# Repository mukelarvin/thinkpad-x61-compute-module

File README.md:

# thinkpad-x61-compute-module
A motherboard replacement for the Thinkpad X61 laptop, using the Raspberry Pi Computer Module

## Display Considerations

Outer Area
Width 268 mm
Height 210 mm

Bottom Bezel 16 mm
Notification LED area 10 mm
Side Bezel 11 mm

Display Viewable Area
Width 246 mm
Height 185 mm

With modifications the bezel could support about...
Width 256 mm
Height 190 mm

### Candidates
SXGA+ Mod
https://www.panelook.com/HV121P01-101_HYDIS_12.1_LCM_overview_3604.html
https://www.panelook.com/HV121P01-100_HYDIS_12.1_LCM_overview_3603.html
Hearted on aliexpress

Wisecoco 11 Inch AMOLED
Width 231.64 mm
Height 168.60 mm
Too small

Surface Pro LCD 12 inch
Width 254 mm
Height 169 mm
Good Candidate, maybe room for Camera?

Ipad Pro 11"
Width 229.06 mm
Height 159.99 mm
A little small

Ipad Pro 12.9"
Width 262 mm
Height 196 mm
This would be a great candidate but the interface is probably quite difficult
https://www.panelook.com/LTL129JL01-A03_Samsung_12.9_Assembly_overview_31582.html

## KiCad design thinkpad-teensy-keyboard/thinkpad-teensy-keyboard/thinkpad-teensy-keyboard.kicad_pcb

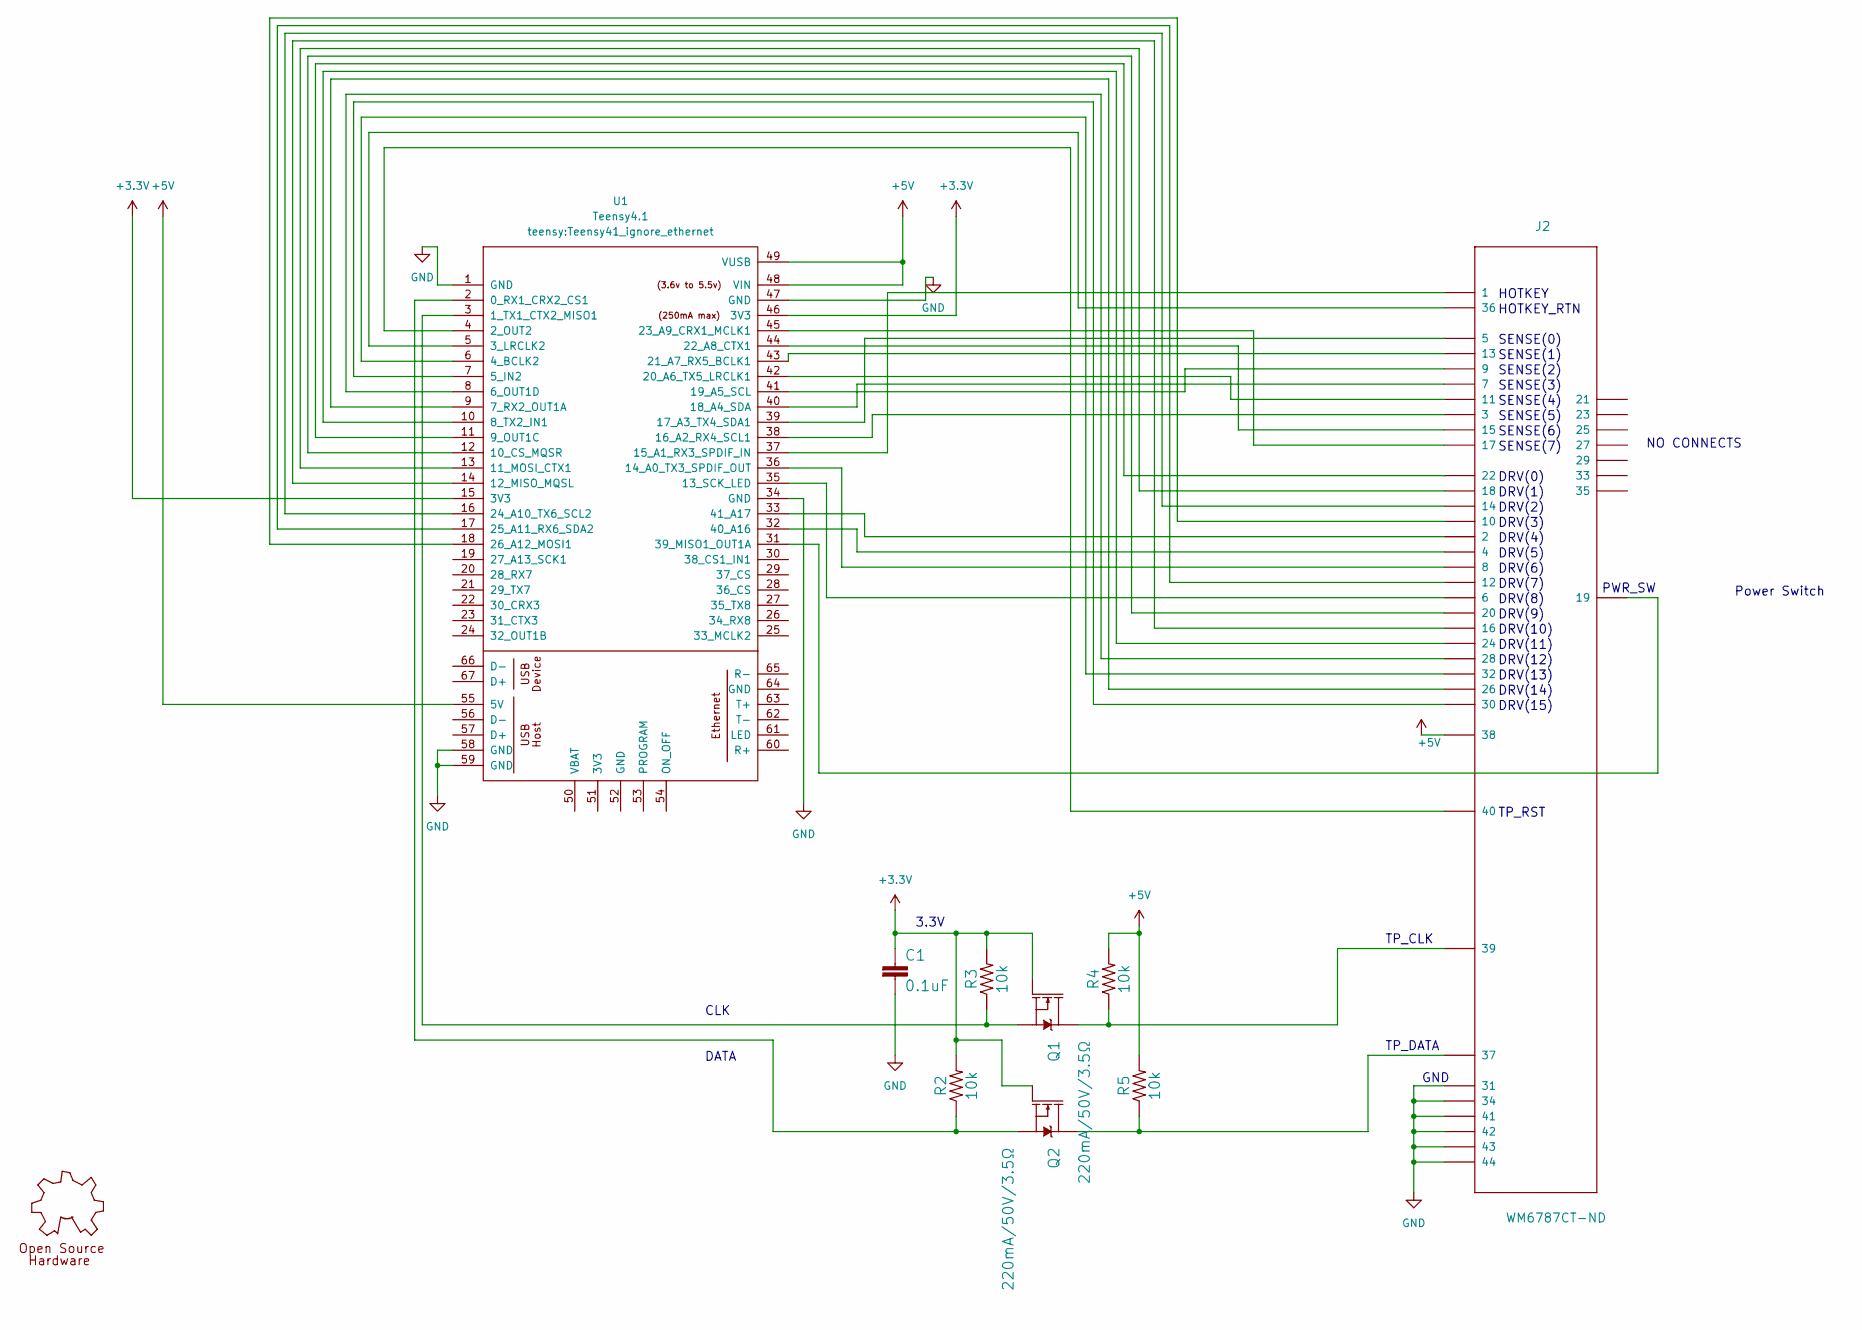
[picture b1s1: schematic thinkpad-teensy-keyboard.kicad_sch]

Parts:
C1: 0.1uF; 0603
GOLD_ORB_SM1: OSHWLOGOLOGO5MM; OSHW_5MM
J2: WM6787CT-ND
Q1, Q2: 220mA/50V/3.5Ω; SOT23-3
R2, R3, R4, R5: 10k; 0603
U1: Teensy4.1; Teensy41_ignore_ethernet

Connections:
+3V3: C1.1, Q1.1 (G), Q2.1 (G), R2.2, R3.2, U1.15 (3V3), U1.46 (3V3)
+5V: J2.P$38 (38), R4.2, R5.2, U1.48 (VIN), U1.49 (VUSB), U1.55 (5V)
GND: C1.2, J2.P$31 (31), J2.P$34 (34), J2.P$41 (43), J2.P$42 (44), J2.P$43 (41), J2.P$44 (42), U1.1 (GND), U1.34 (GND), U1.47 (GND), U1.58 (GND), U1.59 (GND)
unnamed: J2.P$1 (1), U1.37 (15_A1_RX3_SPDIF_IN)
unnamed: J2.P$2 (2), U1.33 (41_A17)
unnamed: J2.P$6 (6), U1.35 (13_SCK_LED)
unnamed: J2.P$8 (8), U1.36 (14_A0_TX3_SPDIF_OUT)
unnamed: J2.P$10 (10), U1.18 (26_A12_MOSI1)
unnamed: J2.P$12 (12), U1.17 (25_A11_RX6_SDA2)
unnamed: J2.P$14 (14), U1.16 (24_A10_TX6_SCL2)
unnamed: J2.P$16 (16), U1.14 (12_MISO_MQSL)
unnamed: J2.P$18 (18), U1.13 (11_MOSI_CTX1)
unnamed: J2.P$19 (19), U1.31 (39_MISO1_OUT1A)
unnamed: J2.P$37 (37), Q2.3 (D), R5.1
unnamed: J2.P$39 (39), Q1.3 (D), R4.1
unnamed: Q1.2 (S), R3.1, U1.3 (1_TX1_CTX2_MISO1)
unnamed: Q2.2 (S), R2.1, U1.2 (0_RX1_CRX2_CS1)
unnamed: J2.P$40 (40), U1.4 (2_OUT2)
unnamed: J2.P$36 (36), U1.5 (3_LRCLK2)
unnamed: J2.P$32 (32), U1.6 (4_BCLK2)
unnamed: J2.P$30 (30), U1.7 (5_IN2)
unnamed: J2.P$28 (28), U1.8 (6_OUT1D)
unnamed: J2.P$26 (26), U1.9 (7_RX2_OUT1A)
unnamed: J2.P$24 (24), U1.10 (8_TX2_IN1)
unnamed: J2.P$22 (22), U1.11 (9_OUT1C)
unnamed: J2.P$20 (20), U1.12 (10_CS_MQSR)
unnamed: J2.P$4 (4), U1.32 (40_A16)
unnamed: J2.P$3 (3), U1.38 (16_A2_RX4_SCL1)
unnamed: J2.P$5 (5), U1.39 (17_A3_TX4_SDA1)
unnamed: J2.P$7 (7), U1.40 (18_A4_SDA)
unnamed: J2.P$9 (9), U1.41 (19_A5_SCL)
unnamed: J2.P$11 (11), U1.42 (20_A6_TX5_LRCLK1)
unnamed: J2.P$13 (13), U1.43 (21_A7_RX5_BCLK1)
unnamed: J2.P$15 (15), U1.44 (22_A8_CTX1)
unnamed: J2.P$17 (17), U1.45 (23_A9_CRX1_MCLK1)

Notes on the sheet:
HOTKEY
DRV(0)
CLK
DRV(4)
DRV(13)
DRV(3)
SENSE(7)
TP_RST
SENSE(0)
TP_DATA
DRV(8)
DRV(6)
DRV(10)
TP_CLK
SENSE(2)
GND
3.3V
SENSE(6)
SENSE(5)
DRV(5)
SENSE(4)
DRV(7)
DRV(2)
DRV(14)
SENSE(3)
PWR_SW
HOTKEY_RTN
SENSE(1)
DRV(9)
DRV(12)
DRV(11)
Power Switch
DRV(1)
DRV(15)
NO CONNECTS
DATA

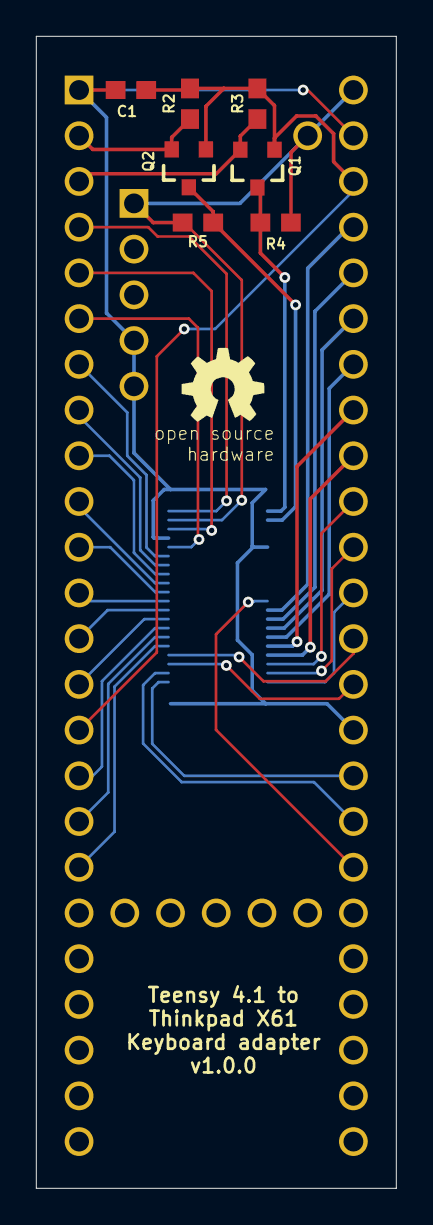
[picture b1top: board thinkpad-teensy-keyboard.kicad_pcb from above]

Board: 2 copper layers, 20.0 x 64.0 mm, 10 parts (1 on the bottom side), 35 nets.

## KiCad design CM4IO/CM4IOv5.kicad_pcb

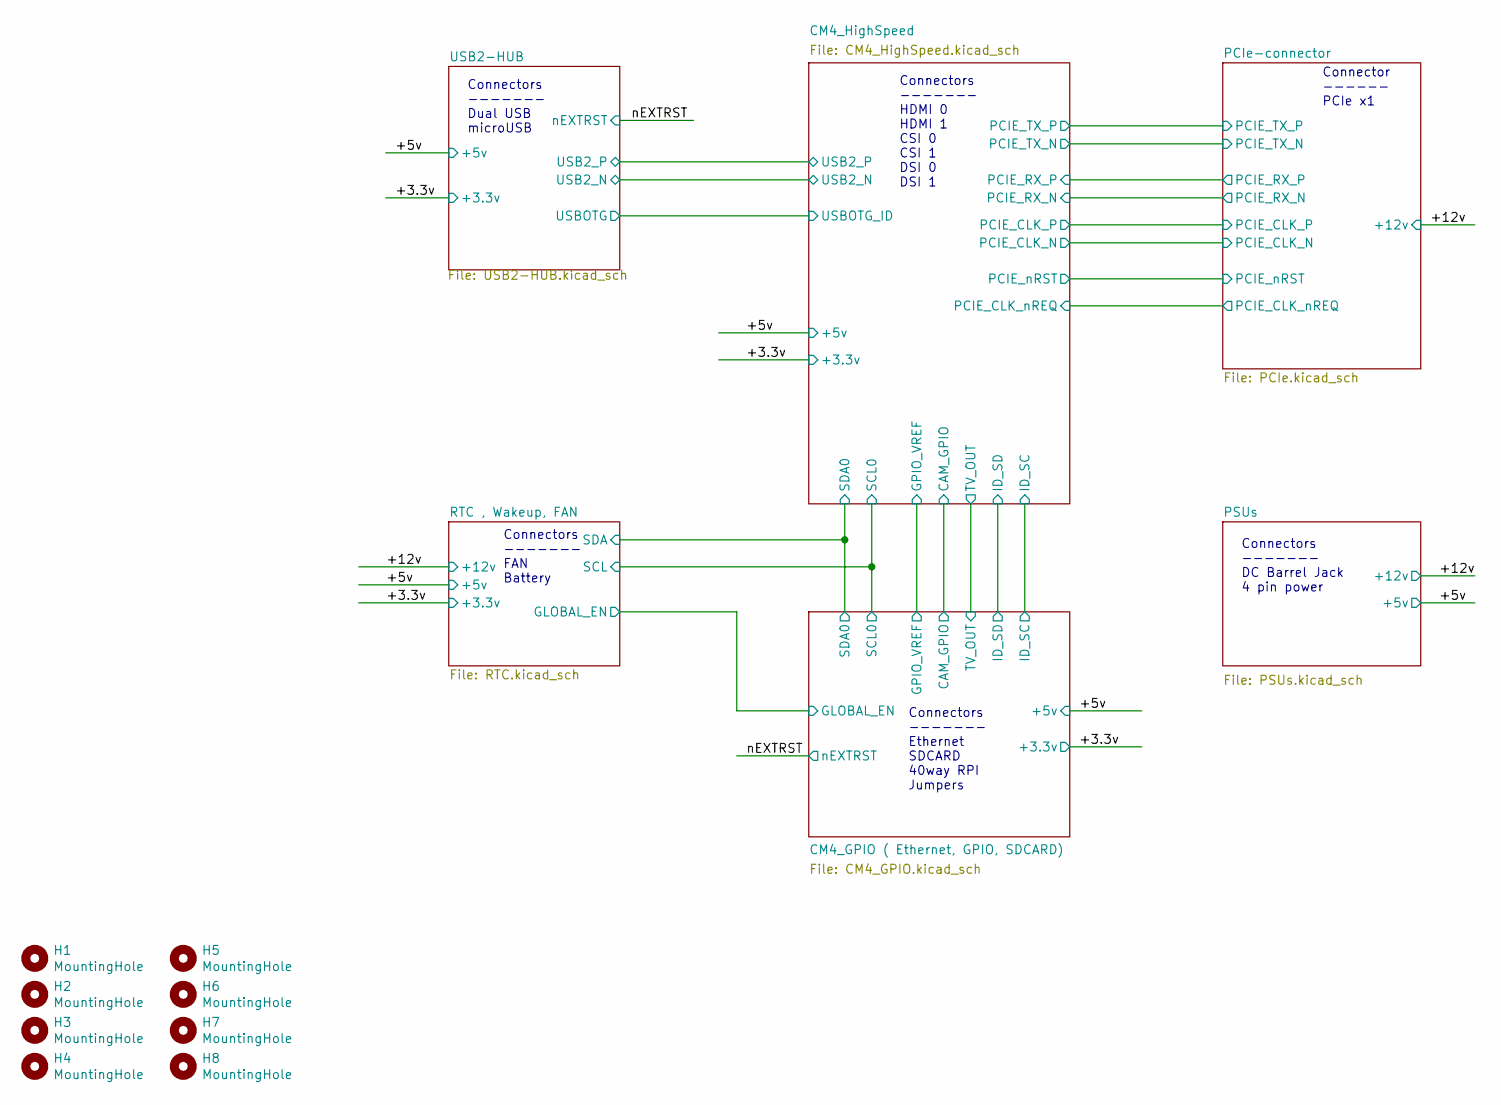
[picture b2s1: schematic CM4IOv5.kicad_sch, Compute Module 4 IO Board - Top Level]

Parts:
H1, H2, H3, H4, H5, H6, H7, H8: MountingHole; MountingHole_2.7mm_M2.5; Part Description M2.5 mounting hole

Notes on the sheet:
Connectors ------- FAN Battery
Connector ------ PCIe x1
Connectors ------- DC Barrel Jack 4 pin power
Connectors ------- Dual USB microUSB
Connectors ------- Ethernet SDCARD 40way RPI Jumpers
Connectors ------- HDMI 0 HDMI 1 CSI 0 CSI 1 DSI 0 DSI 1

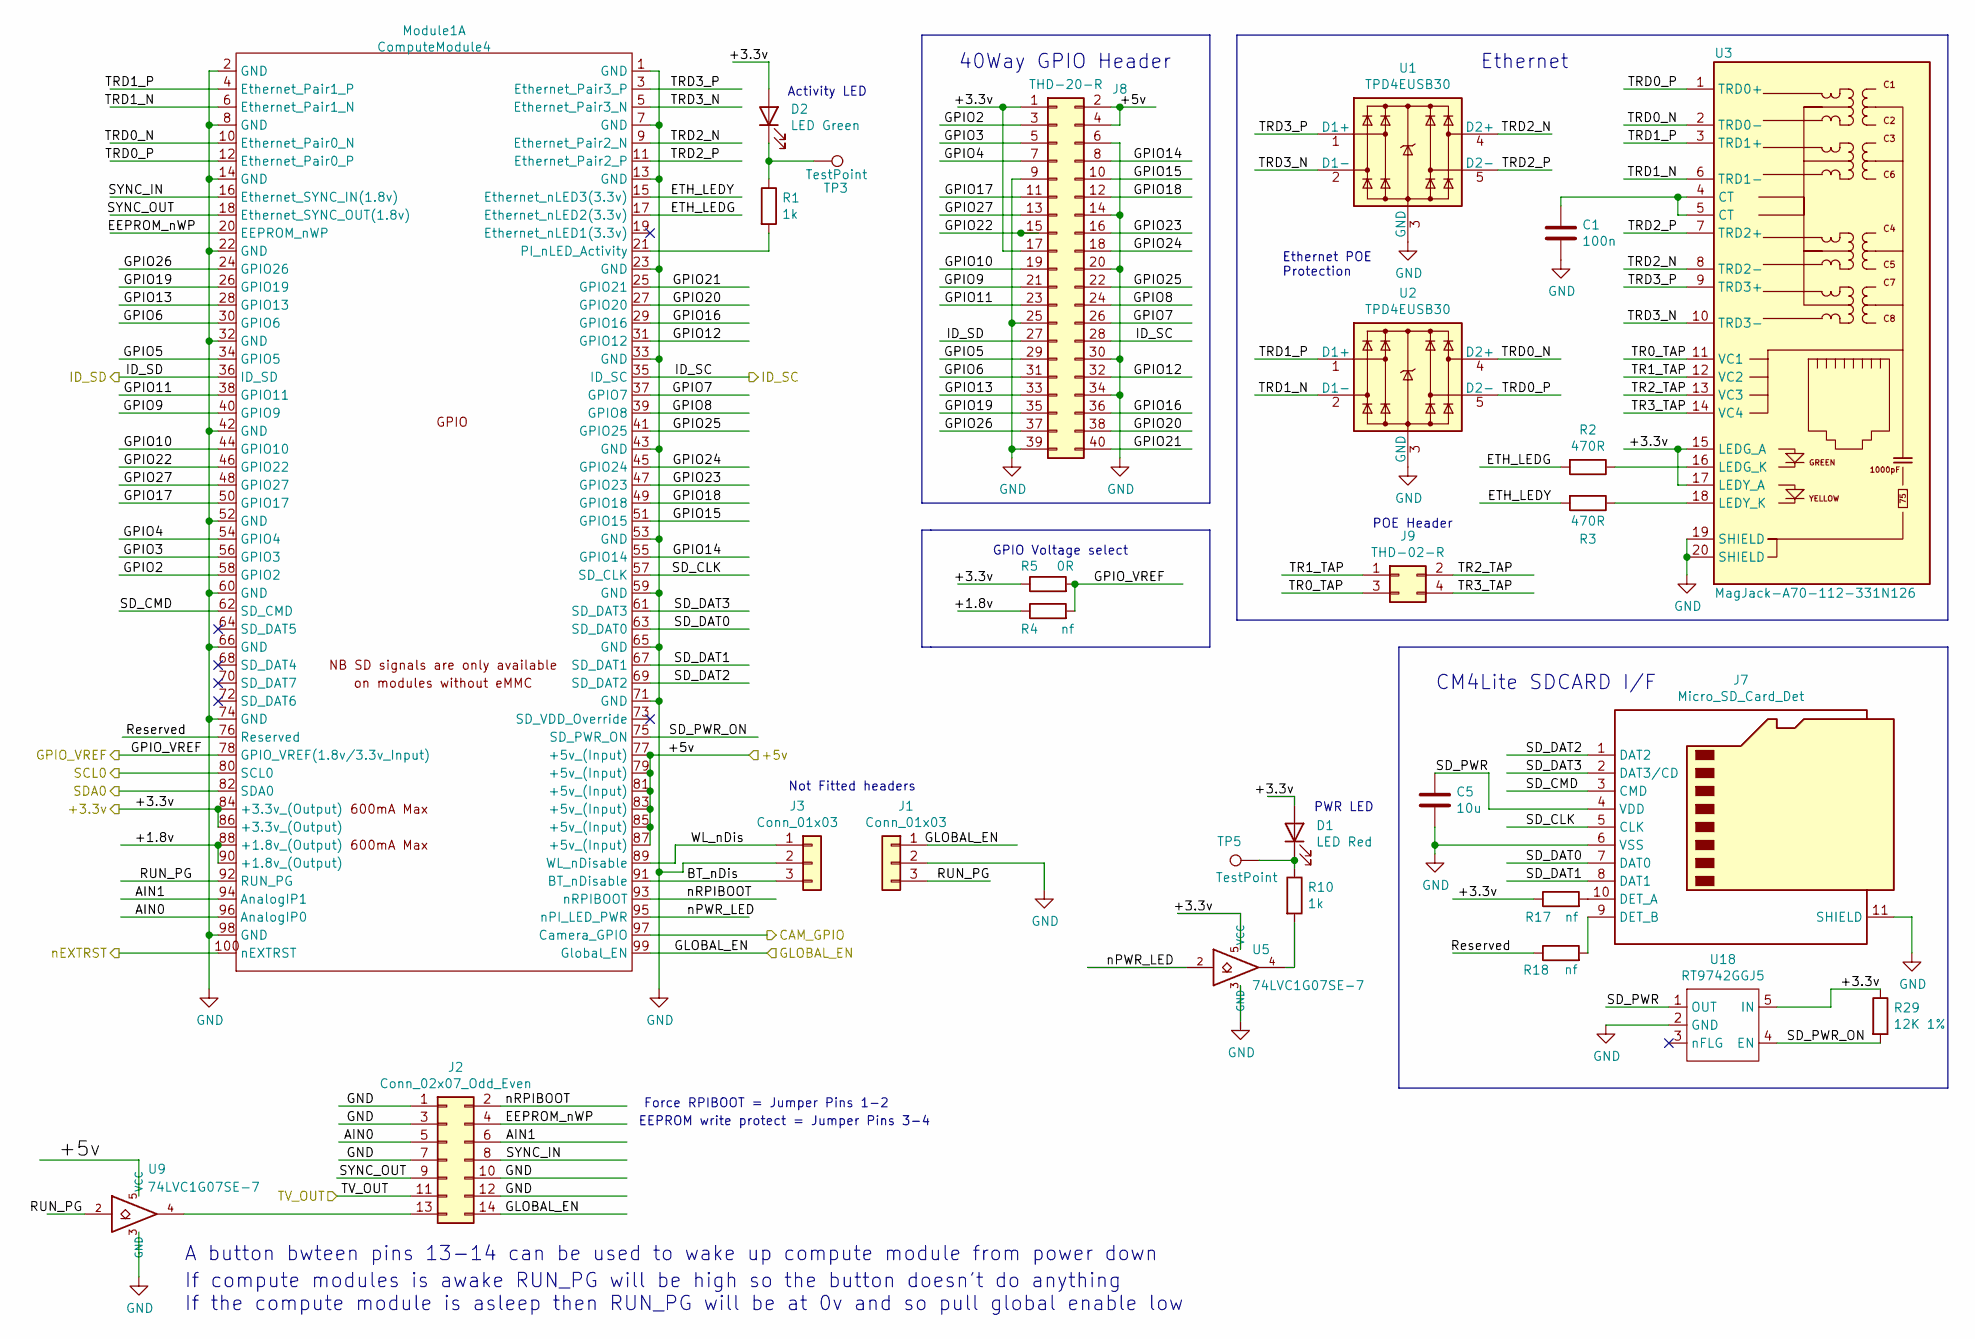
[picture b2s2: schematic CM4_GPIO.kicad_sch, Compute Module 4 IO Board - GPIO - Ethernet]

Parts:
C1: 100n; C_0402_1005Metric; Part Description 0.1uF 10% 16V Ceramic Capacitor X7R 040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
C5: 10u; C_0805_2012Metric; Part Description 10uF 10% 10V Ceramic Capacitor X7R 0805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
D1: LED Red; LED_0603_1608Metric; Part Description Red 620nm LED Indication - Discrete 2.2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
D2: LED Green; LED_0603_1608Metric; Part Description Green 572nm LED Indication - Discrete 2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
J1, J3: Conn_01x03; PinHeader_1x03_P2.54mm_Vertical; Part Description 3pin 0.1" connector
J2: Conn_02x07_Odd_Even; PinHeader_2x07_P2.54mm_Vertical; Part Description PinHeader_2x07_P2.54mm_Vertical
J7: Micro_SD_Card_Det; SDCARD_MOLEX_503398-1892; Part Description 9 (8 + 1) Position Card Connector micro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
J8: THD-20-R; PinHeader_2x20_P2.54mm_Vertical; Part Description PinHeader_2x20_P2.54mm_Vertical
J9: THD-02-R; PinHeader_2x02_P2.54mm_Vertical; Part Description PinHeader_2x02_P2.54mm_Vertical
Module1: ComputeModule4; Raspberry-Pi-4-Compute-Module; Part Description 100 Position Connector Receptacle, Cent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
R1, R10: 1k; R_0402_1005Metric; Part Description Resistor 1K M1005 1% 63mW
R2, R3: 470R; R_0402_1005Metric; Part Description Resistor 470R M1005 1% 63mW
R4: nf; R_0805_2012Metric_Pad1.15x1.40mm_HandSolder
R5: 0R; R_0805_2012Metric_Pad1.15x1.40mm_HandSolder; Part Description Resistor 0R M2012 5%
R17, R18: nf; R_0402_1005Metric; Part Description Resistor 1K M1005 1% 63mW
R29: 12K 1%; R_0402_1005Metric; Part Description Resistor 12K M1005 1% 63mW
TP3, TP5: TestPoint; TestPoint_Pad_2.0x2.0mm
U1, U2: TPD4EUSB30; USON-10_2.5x1.0mm_P0.5mm; Part Description Quad TVS diode for high speed signals (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
U3: MagJack-A70-112-331N126; TRJG0926HENL; Part Description Gigabit Ethernet Magjack
U5, U9: 74LVC1G07SE-7; SOT-353_SC-70-5; Part Description Buffer, Non-Inverting 1 Element 1 Bit p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
U18: RT9742GGJ5; SOT-23-5; Part Description Power Switch/Driver 1:1 N-Channel 1A TS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

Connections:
/+3.3v: D1.2 (A), D2.2 (A), J8.1, J8.17, Module1.84 (+3.3v_(Output)), Module1.86 (+3.3v_(Output)), R5.1, R17.1, R29.1, U3.15 (LEDG_A), U3.17 (LEDY_A), U5.5 (VCC), U18.5 (IN); also elsewhere on the board
/+5v: J8.2, J8.4, Module1.77 (+5v_(Input)), Module1.79 (+5v_(Input)), Module1.81 (+5v_(Input)), Module1.83 (+5v_(Input)), Module1.85 (+5v_(Input)), Module1.87 (+5v_(Input)), U9.5 (VCC); also elsewhere on the board
/CAM_GPIO: Module1.97 (Camera_GPIO); also elsewhere on the board
/CM4_GPIO ( Ethernet, GPIO, SDCARD)/+1.8v: Module1.88 (+1.8v_(Output)), Module1.90 (+1.8v_(Output)), R4.1
/CM4_GPIO ( Ethernet, GPIO, SDCARD)/AIN0: J2.5, Module1.96 (AnalogIP0)
/CM4_GPIO ( Ethernet, GPIO, SDCARD)/AIN1: J2.6, Module1.94 (AnalogIP1)
/CM4_GPIO ( Ethernet, GPIO, SDCARD)/BT_nDis: J3.3, Module1.91 (BT_nDisable)
/CM4_GPIO ( Ethernet, GPIO, SDCARD)/EEPROM_nWP: J2.4, Module1.20 (EEPROM_nWP)
/CM4_GPIO ( Ethernet, GPIO, SDCARD)/ETH_LEDG: Module1.17 (Ethernet_nLED2(3.3v)), R2.2
/CM4_GPIO ( Ethernet, GPIO, SDCARD)/ETH_LEDY: Module1.15 (Ethernet_nLED3(3.3v)), R3.2
/CM4_GPIO ( Ethernet, GPIO, SDCARD)/GPIO2: J8.3, Module1.58 (GPIO2)
/CM4_GPIO ( Ethernet, GPIO, SDCARD)/GPIO3: J8.5, Module1.56 (GPIO3)
/CM4_GPIO ( Ethernet, GPIO, SDCARD)/GPIO4: J8.7, Module1.54 (GPIO4)
/CM4_GPIO ( Ethernet, GPIO, SDCARD)/GPIO5: J8.29, Module1.34 (GPIO5)
/CM4_GPIO ( Ethernet, GPIO, SDCARD)/GPIO6: J8.31, Module1.30 (GPIO6)
/CM4_GPIO ( Ethernet, GPIO, SDCARD)/GPIO7: J8.26, Module1.37 (GPIO7)
/CM4_GPIO ( Ethernet, GPIO, SDCARD)/GPIO8: J8.24, Module1.39 (GPIO8)
/CM4_GPIO ( Ethernet, GPIO, SDCARD)/GPIO9: J8.21, Module1.40 (GPIO9)
/CM4_GPIO ( Ethernet, GPIO, SDCARD)/GPIO10: J8.19, Module1.44 (GPIO10)
/CM4_GPIO ( Ethernet, GPIO, SDCARD)/GPIO11: J8.23, Module1.38 (GPIO11)
/CM4_GPIO ( Ethernet, GPIO, SDCARD)/GPIO12: J8.32, Module1.31 (GPIO12)
/CM4_GPIO ( Ethernet, GPIO, SDCARD)/GPIO13: J8.33, Module1.28 (GPIO13)
/CM4_GPIO ( Ethernet, GPIO, SDCARD)/GPIO14: J8.8, Module1.55 (GPIO14)
/CM4_GPIO ( Ethernet, GPIO, SDCARD)/GPIO15: J8.10, Module1.51 (GPIO15)
/CM4_GPIO ( Ethernet, GPIO, SDCARD)/GPIO16: J8.36, Module1.29 (GPIO16)
/CM4_GPIO ( Ethernet, GPIO, SDCARD)/GPIO17: J8.11, Module1.50 (GPIO17)
/CM4_GPIO ( Ethernet, GPIO, SDCARD)/GPIO18: J8.12, Module1.49 (GPIO18)
/CM4_GPIO ( Ethernet, GPIO, SDCARD)/GPIO19: J8.35, Module1.26 (GPIO19)
/CM4_GPIO ( Ethernet, GPIO, SDCARD)/GPIO20: J8.38, Module1.27 (GPIO20)
/CM4_GPIO ( Ethernet, GPIO, SDCARD)/GPIO21: J8.40, Module1.25 (GPIO21)
/CM4_GPIO ( Ethernet, GPIO, SDCARD)/GPIO22: J8.15, Module1.46 (GPIO22)
/CM4_GPIO ( Ethernet, GPIO, SDCARD)/GPIO23: J8.16, Module1.47 (GPIO23)
/CM4_GPIO ( Ethernet, GPIO, SDCARD)/GPIO24: J8.18, Module1.45 (GPIO24)
/CM4_GPIO ( Ethernet, GPIO, SDCARD)/GPIO25: J8.22, Module1.41 (GPIO25)
/CM4_GPIO ( Ethernet, GPIO, SDCARD)/GPIO26: J8.37, Module1.24 (GPIO26)
/CM4_GPIO ( Ethernet, GPIO, SDCARD)/GPIO27: J8.13, Module1.48 (GPIO27)
/CM4_GPIO ( Ethernet, GPIO, SDCARD)/RUN_PG: J1.3, Module1.92 (RUN_PG), U9.2
/CM4_GPIO ( Ethernet, GPIO, SDCARD)/Reserved: Module1.76 (Reserved), R18.1
/CM4_GPIO ( Ethernet, GPIO, SDCARD)/SD_CLK: J7.5 (CLK), Module1.57 (SD_CLK)
/CM4_GPIO ( Ethernet, GPIO, SDCARD)/SD_CMD: J7.3 (CMD), Module1.62 (SD_CMD)
/CM4_GPIO ( Ethernet, GPIO, SDCARD)/SD_DAT0: J7.7 (DAT0), Module1.63 (SD_DAT0)
/CM4_GPIO ( Ethernet, GPIO, SDCARD)/SD_DAT1: J7.8 (DAT1), Module1.67 (SD_DAT1)
/CM4_GPIO ( Ethernet, GPIO, SDCARD)/SD_DAT2: J7.1 (DAT2), Module1.69 (SD_DAT2)
/CM4_GPIO ( Ethernet, GPIO, SDCARD)/SD_DAT3: J7.2 (DAT3/CD), Module1.61 (SD_DAT3)
/CM4_GPIO ( Ethernet, GPIO, SDCARD)/SD_PWR: C5.1, J7.4 (VDD), U18.1 (OUT)
/CM4_GPIO ( Ethernet, GPIO, SDCARD)/SD_PWR_ON: Module1.75 (SD_PWR_ON), R29.2, U18.4 (EN)
/CM4_GPIO ( Ethernet, GPIO, SDCARD)/SYNC_IN: J2.8, Module1.16 (Ethernet_SYNC_IN(1.8v))
/CM4_GPIO ( Ethernet, GPIO, SDCARD)/SYNC_OUT: J2.9, Module1.18 (Ethernet_SYNC_OUT(1.8v))
/CM4_GPIO ( Ethernet, GPIO, SDCARD)/TR0_TAP: J9.3, U3.11 (VC1)
/CM4_GPIO ( Ethernet, GPIO, SDCARD)/TR1_TAP: J9.1, U3.12 (VC2)
/CM4_GPIO ( Ethernet, GPIO, SDCARD)/TR2_TAP: J9.2, U3.13 (VC3)
/CM4_GPIO ( Ethernet, GPIO, SDCARD)/TR3_TAP: J9.4, U3.14 (VC4)
/CM4_GPIO ( Ethernet, GPIO, SDCARD)/TRD0_N: Module1.10 (Ethernet_Pair0_N), U2.4 (D2+), U2.7, U3.2 (TRD0-)
/CM4_GPIO ( Ethernet, GPIO, SDCARD)/TRD0_P: Module1.12 (Ethernet_Pair0_P), U2.5 (D2-), U2.6, U3.1 (TRD0+)
/CM4_GPIO ( Ethernet, GPIO, SDCARD)/TRD1_N: Module1.6 (Ethernet_Pair1_N), U2.2 (D1-), U2.9, U3.6 (TRD1-)
/CM4_GPIO ( Ethernet, GPIO, SDCARD)/TRD1_P: Module1.4 (Ethernet_Pair1_P), U2.1 (D1+), U2.10, U3.3 (TRD1+)
/CM4_GPIO ( Ethernet, GPIO, SDCARD)/TRD2_N: Module1.9 (Ethernet_Pair2_N), U1.4 (D2+), U1.7, U3.8 (TRD2-)
/CM4_GPIO ( Ethernet, GPIO, SDCARD)/TRD2_P: Module1.11 (Ethernet_Pair2_P), U1.5 (D2-), U1.6, U3.7 (TRD2+)
/CM4_GPIO ( Ethernet, GPIO, SDCARD)/TRD3_N: Module1.5 (Ethernet_Pair3_N), U1.2 (D1-), U1.9, U3.10 (TRD3-)
/CM4_GPIO ( Ethernet, GPIO, SDCARD)/TRD3_P: Module1.3 (Ethernet_Pair3_P), U1.1 (D1+), U1.10, U3.9 (TRD3+)
/CM4_GPIO ( Ethernet, GPIO, SDCARD)/WL_nDis: J3.1, Module1.89 (WL_nDisable)
/CM4_GPIO ( Ethernet, GPIO, SDCARD)/nPWR_LED: Module1.95 (nPI_LED_PWR), U5.2
/CM4_GPIO ( Ethernet, GPIO, SDCARD)/nRPIBOOT: J2.2, Module1.93 (nRPIBOOT)
/GLOBAL_EN: J1.1, J2.14, Module1.99 (Global_EN); also elsewhere on the board
/GPIO_VREF: Module1.78 (GPIO_VREF(1.8v/3.3v_Input)), R4.2, R5.2; also elsewhere on the board
/ID_SC: J8.28, Module1.35 (ID_SC); also elsewhere on the board
/ID_SD: J8.27, Module1.36 (ID_SD); also elsewhere on the board
/SCL0: Module1.80 (SCL0); also elsewhere on the board
/SDA0: Module1.82 (SDA0); also elsewhere on the board
/TV_OUT: J2.11; also elsewhere on the board
/nEXTRST: Module1.100 (nEXTRST); also elsewhere on the board
unnamed: C1.1, U3.4 (CT), U3.5 (CT)
unnamed: D1.1 (K), R10.1, TP5.1
unnamed: D2.1 (K), R1.1, TP3.1
unnamed: J2.13, U9.4
unnamed: J7.9 (DET_B), R18.2
unnamed: J7.10 (DET_A), R17.2
unnamed: Module1.21 (PI_nLED_Activity), R1.2
unnamed: R2.1, U3.16 (LEDG_K)
unnamed: R3.1, U3.18 (LEDY_K)
unnamed: R10.2, U5.4

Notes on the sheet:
PWR LED
Ethernet POE Protection
40Way GPIO Header
CM4Lite SDCARD I/F
GPIO Voltage select
Ethernet
Activity LED
EEPROM write protect = Jumper Pins 3-4
Not Fitted headers
A button bwteen pins 13-14 can be used to wake up compute module from power down
If compute modules is awake RUN_PG will be high so the button doesn't do anything If the compute module is asleep then RUN_PG will be at 0v and so pull global enable low
Force RPIBOOT = Jumper Pins 1-2
POE Header

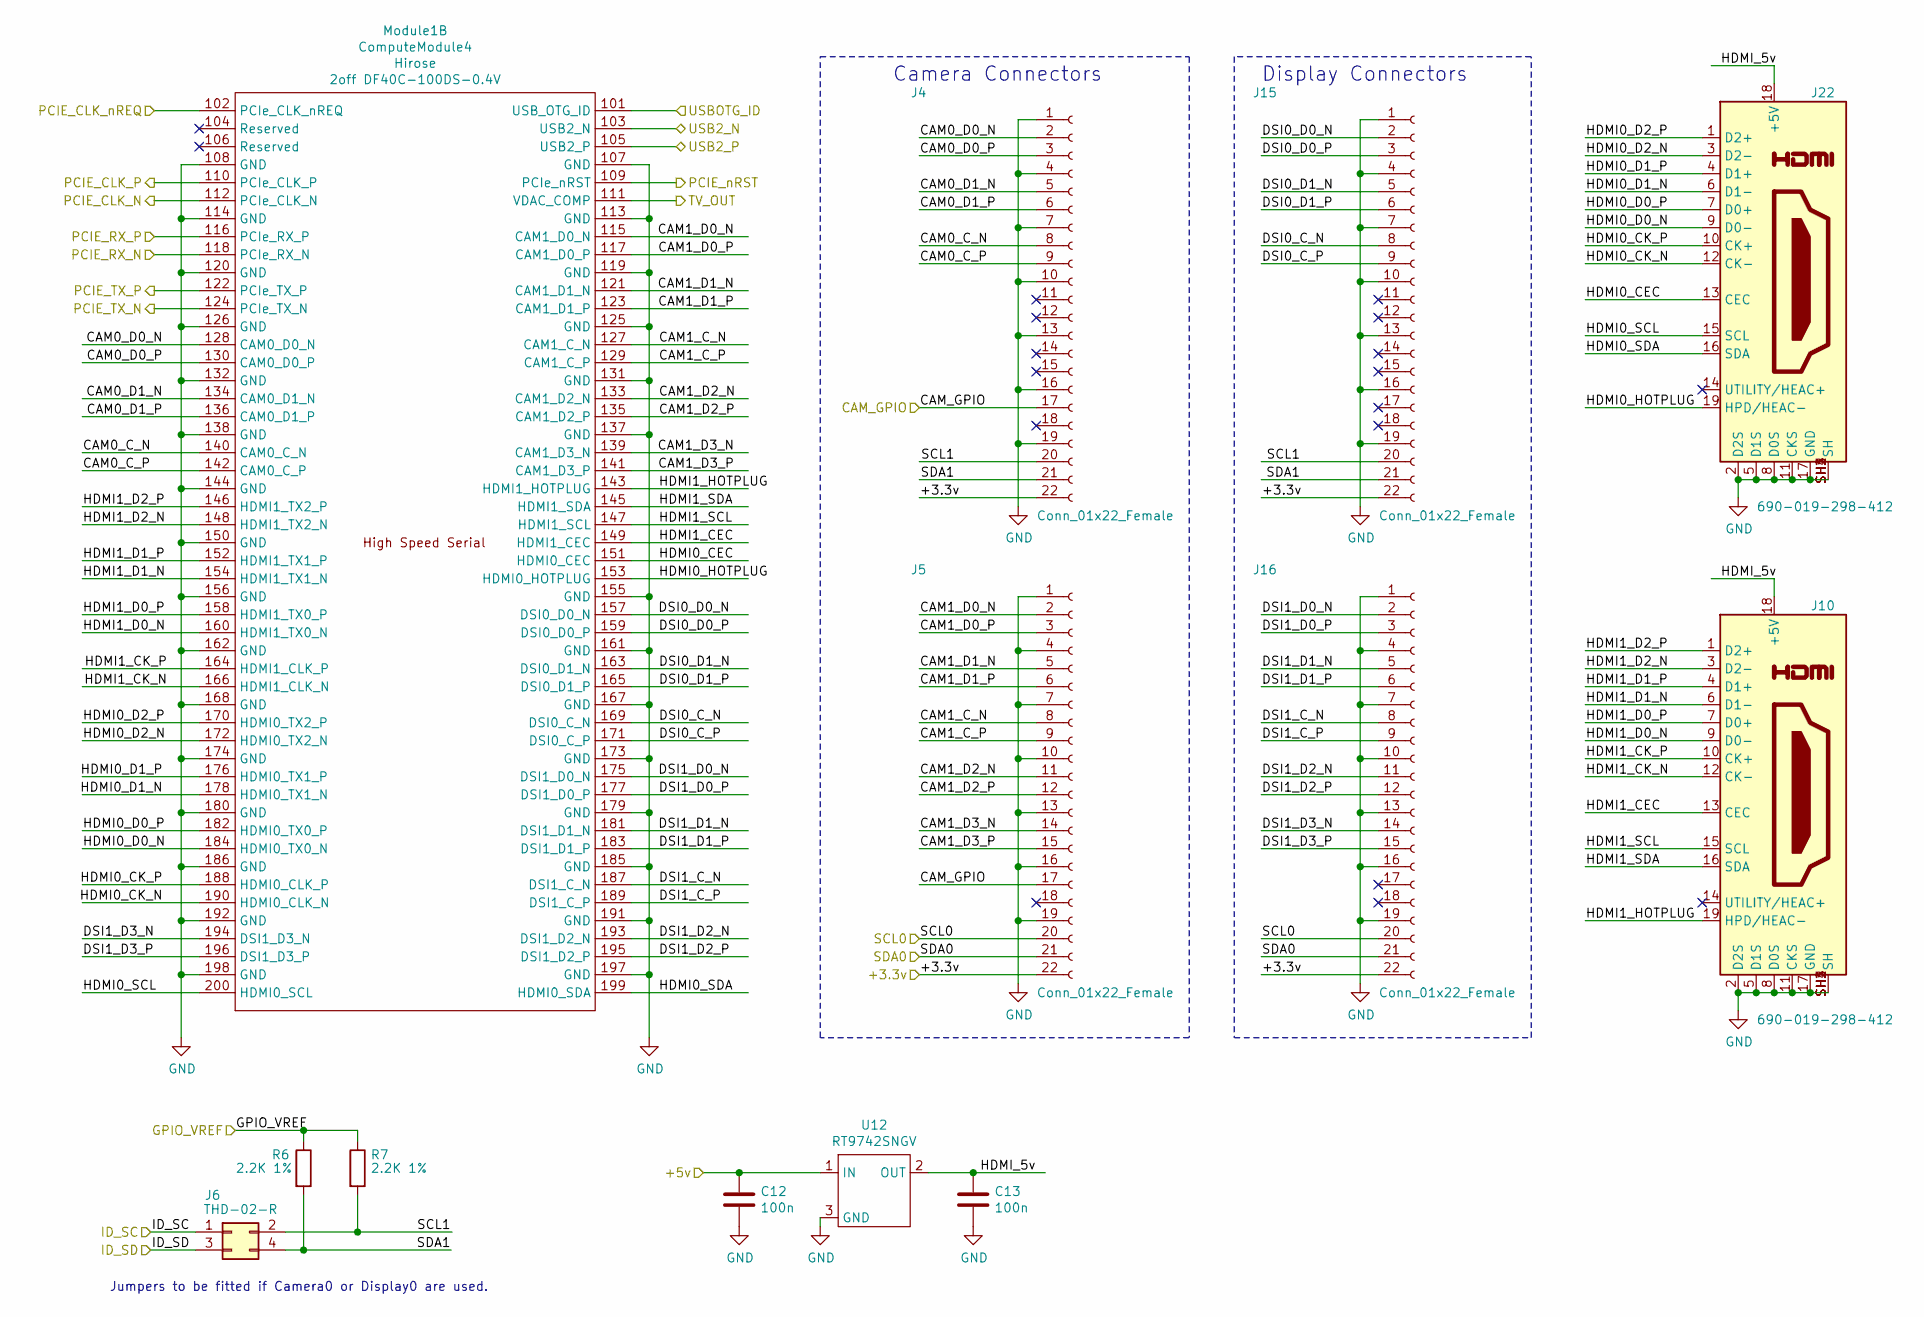
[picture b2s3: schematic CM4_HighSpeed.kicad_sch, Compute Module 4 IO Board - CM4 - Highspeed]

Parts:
C12, C13: 100n; C_0402_1005Metric; Part Description 0.1uF 10% 16V Ceramic Capacitor X7R 040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
J4, J5, J15, J16: Conn_01x22_Female; Hirose_FH12-22S-0.5SH_1x22-1MP_P0.50mm_Horizontal; Part Description 22 Position FFC, FPC Connector Contacts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
J6: THD-02-R; PinHeader_2x02_P2.54mm_Vertical; Part Description PinHeader_2x02_P2.54mm_Vertical
J10, J22: 690-019-298-412; EDAC 690-019-298-412; Part Description HDMI Connector, Right Angle, 19 Contact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
Module1: ComputeModule4; Raspberry-Pi-4-Compute-Module; Part Description 100 Position Connector Receptacle, Cent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
R6, R7: 2.2K 1%; R_0402_1005Metric; Part Description Resistor 2.2K M1005 1% 63mW
U12: RT9742SNGV; SOT-23; Part Description Power Switch/Driver 1:1 N-Channel 500mA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

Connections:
/+3.3v: J4.22, J5.22, J15.22, J16.22; also elsewhere on the board
/+5v: C12.1, U12.1 (IN); also elsewhere on the board
/CAM_GPIO: J4.17, J5.17; also elsewhere on the board
/CM4_HighSpeed/CAM0_C_N: J4.8, Module1.140 (CAM0_C_N)
/CM4_HighSpeed/CAM0_C_P: J4.9, Module1.142 (CAM0_C_P)
/CM4_HighSpeed/CAM0_D0_N: J4.2, Module1.128 (CAM0_D0_N)
/CM4_HighSpeed/CAM0_D0_P: J4.3, Module1.130 (CAM0_D0_P)
/CM4_HighSpeed/CAM0_D1_N: J4.5, Module1.134 (CAM0_D1_N)
/CM4_HighSpeed/CAM0_D1_P: J4.6, Module1.136 (CAM0_D1_P)
/CM4_HighSpeed/CAM1_C_N: J5.8, Module1.127 (CAM1_C_N)
/CM4_HighSpeed/CAM1_C_P: J5.9, Module1.129 (CAM1_C_P)
/CM4_HighSpeed/CAM1_D0_N: J5.2, Module1.115 (CAM1_D0_N)
/CM4_HighSpeed/CAM1_D0_P: J5.3, Module1.117 (CAM1_D0_P)
/CM4_HighSpeed/CAM1_D1_N: J5.5, Module1.121 (CAM1_D1_N)
/CM4_HighSpeed/CAM1_D1_P: J5.6, Module1.123 (CAM1_D1_P)
/CM4_HighSpeed/CAM1_D2_N: J5.11, Module1.133 (CAM1_D2_N)
/CM4_HighSpeed/CAM1_D2_P: J5.12, Module1.135 (CAM1_D2_P)
/CM4_HighSpeed/CAM1_D3_N: J5.14, Module1.139 (CAM1_D3_N)
/CM4_HighSpeed/CAM1_D3_P: J5.15, Module1.141 (CAM1_D3_P)
/CM4_HighSpeed/DSI0_C_N: J15.8, Module1.169 (DSI0_C_N)
/CM4_HighSpeed/DSI0_C_P: J15.9, Module1.171 (DSI0_C_P)
/CM4_HighSpeed/DSI0_D0_N: J15.2, Module1.157 (DSI0_D0_N)
/CM4_HighSpeed/DSI0_D0_P: J15.3, Module1.159 (DSI0_D0_P)
/CM4_HighSpeed/DSI0_D1_N: J15.5, Module1.163 (DSI0_D1_N)
/CM4_HighSpeed/DSI0_D1_P: J15.6, Module1.165 (DSI0_D1_P)
/CM4_HighSpeed/DSI1_C_N: J16.8, Module1.187 (DSI1_C_N)
/CM4_HighSpeed/DSI1_C_P: J16.9, Module1.189 (DSI1_C_P)
/CM4_HighSpeed/DSI1_D0_N: J16.2, Module1.175 (DSI1_D0_N)
/CM4_HighSpeed/DSI1_D0_P: J16.3, Module1.177 (DSI1_D0_P)
/CM4_HighSpeed/DSI1_D1_N: J16.5, Module1.181 (DSI1_D1_N)
/CM4_HighSpeed/DSI1_D1_P: J16.6, Module1.183 (DSI1_D1_P)
/CM4_HighSpeed/DSI1_D2_N: J16.11, Module1.193 (DSI1_D2_N)
/CM4_HighSpeed/DSI1_D2_P: J16.12, Module1.195 (DSI1_D2_P)
/CM4_HighSpeed/DSI1_D3_N: J16.14, Module1.194 (DSI1_D3_N)
/CM4_HighSpeed/DSI1_D3_P: J16.15, Module1.196 (DSI1_D3_P)
/CM4_HighSpeed/HDMI0_CEC: J22.13 (CEC), Module1.151 (HDMI0_CEC)
/CM4_HighSpeed/HDMI0_CK_N: J22.12 (CK-), Module1.190 (HDMI0_CLK_N)
/CM4_HighSpeed/HDMI0_CK_P: J22.10 (CK+), Module1.188 (HDMI0_CLK_P)
/CM4_HighSpeed/HDMI0_D0_N: J22.9 (D0-), Module1.184 (HDMI0_TX0_N)
/CM4_HighSpeed/HDMI0_D0_P: J22.7 (D0+), Module1.182 (HDMI0_TX0_P)
/CM4_HighSpeed/HDMI0_D1_N: J22.6 (D1-), Module1.178 (HDMI0_TX1_N)
/CM4_HighSpeed/HDMI0_D1_P: J22.4 (D1+), Module1.176 (HDMI0_TX1_P)
/CM4_HighSpeed/HDMI0_D2_N: J22.3 (D2-), Module1.172 (HDMI0_TX2_N)
/CM4_HighSpeed/HDMI0_D2_P: J22.1 (D2+), Module1.170 (HDMI0_TX2_P)
/CM4_HighSpeed/HDMI0_HOTPLUG: J22.19 (HPD/HEAC-), Module1.153 (HDMI0_HOTPLUG)
/CM4_HighSpeed/HDMI0_SCL: J22.15 (SCL), Module1.200 (HDMI0_SCL)
/CM4_HighSpeed/HDMI0_SDA: J22.16 (SDA), Module1.199 (HDMI0_SDA)
/CM4_HighSpeed/HDMI1_CEC: J10.13 (CEC), Module1.149 (HDMI1_CEC)
/CM4_HighSpeed/HDMI1_CK_N: J10.12 (CK-), Module1.166 (HDMI1_CLK_N)
/CM4_HighSpeed/HDMI1_CK_P: J10.10 (CK+), Module1.164 (HDMI1_CLK_P)
/CM4_HighSpeed/HDMI1_D0_N: J10.9 (D0-), Module1.160 (HDMI1_TX0_N)
/CM4_HighSpeed/HDMI1_D0_P: J10.7 (D0+), Module1.158 (HDMI1_TX0_P)
/CM4_HighSpeed/HDMI1_D1_N: J10.6 (D1-), Module1.154 (HDMI1_TX1_N)
/CM4_HighSpeed/HDMI1_D1_P: J10.4 (D1+), Module1.152 (HDMI1_TX1_P)
/CM4_HighSpeed/HDMI1_D2_N: J10.3 (D2-), Module1.148 (HDMI1_TX2_N)
/CM4_HighSpeed/HDMI1_D2_P: J10.1 (D2+), Module1.146 (HDMI1_TX2_P)
/CM4_HighSpeed/HDMI1_HOTPLUG: J10.19 (HPD/HEAC-), Module1.143 (HDMI1_HOTPLUG)
/CM4_HighSpeed/HDMI1_SCL: J10.15 (SCL), Module1.147 (HDMI1_SCL)
/CM4_HighSpeed/HDMI1_SDA: J10.16 (SDA), Module1.145 (HDMI1_SDA)
/CM4_HighSpeed/HDMI_5v: C13.1, J10.18 (+5V), J22.18 (+5V), U12.2 (OUT)
/CM4_HighSpeed/SCL1: J4.20, J6.2, J15.20, R7.2
/CM4_HighSpeed/SDA1: J4.21, J6.4, J15.21, R6.2
/GPIO_VREF: R6.1, R7.1; also elsewhere on the board
/ID_SC: J6.1; also elsewhere on the board
/ID_SD: J6.3; also elsewhere on the board
/PCIE_CLK_N: Module1.112 (PCIe_CLK_N); also elsewhere on the board
/PCIE_CLK_P: Module1.110 (PCIe_CLK_P); also elsewhere on the board
/PCIE_CLK_nREQ: Module1.102 (PCIe_CLK_nREQ); also elsewhere on the board
/PCIE_RX_N: Module1.118 (PCIe_RX_N); also elsewhere on the board
/PCIE_RX_P: Module1.116 (PCIe_RX_P); also elsewhere on the board
/PCIE_TX_N: Module1.124 (PCIe_TX_N); also elsewhere on the board
/PCIE_TX_P: Module1.122 (PCIe_TX_P); also elsewhere on the board
/PCIE_nRST: Module1.109 (PCIe_nRST); also elsewhere on the board
/SCL0: J5.20, J16.20; also elsewhere on the board
/SDA0: J5.21, J16.21; also elsewhere on the board
/TV_OUT: Module1.111 (VDAC_COMP); also elsewhere on the board
/USB2_N: Module1.103 (USB2_N); also elsewhere on the board
/USB2_P: Module1.105 (USB2_P); also elsewhere on the board
/USBOTG: Module1.101 (USB_OTG_ID); also elsewhere on the board

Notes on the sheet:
Jumpers to be fitted if Camera0 or Display0 are used.
Camera Connectors
Display Connectors

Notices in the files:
CM4IO/CM4IOv5.kicad_sch:
© 2020-2022 Raspberry Pi Ltd (formerly Raspberry Pi (Trading) Ltd.)
